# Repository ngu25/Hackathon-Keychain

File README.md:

# Hackathon-Keychain

This is a keychain made for the participants and giveaway!

This event & the keychain wouldn't have been possible without the amazing [team](https://www.linkedin.com/posts/srinivasan-m-421179179_hackathon-pcbcupid-glyph-activity-7355658636741758976-tHrb?utm_source=share&utm_medium=member_desktop&rcm=ACoAADTSA38BsfCnTXBQPUgEnAOWLHQZu77Voxg) that we had!

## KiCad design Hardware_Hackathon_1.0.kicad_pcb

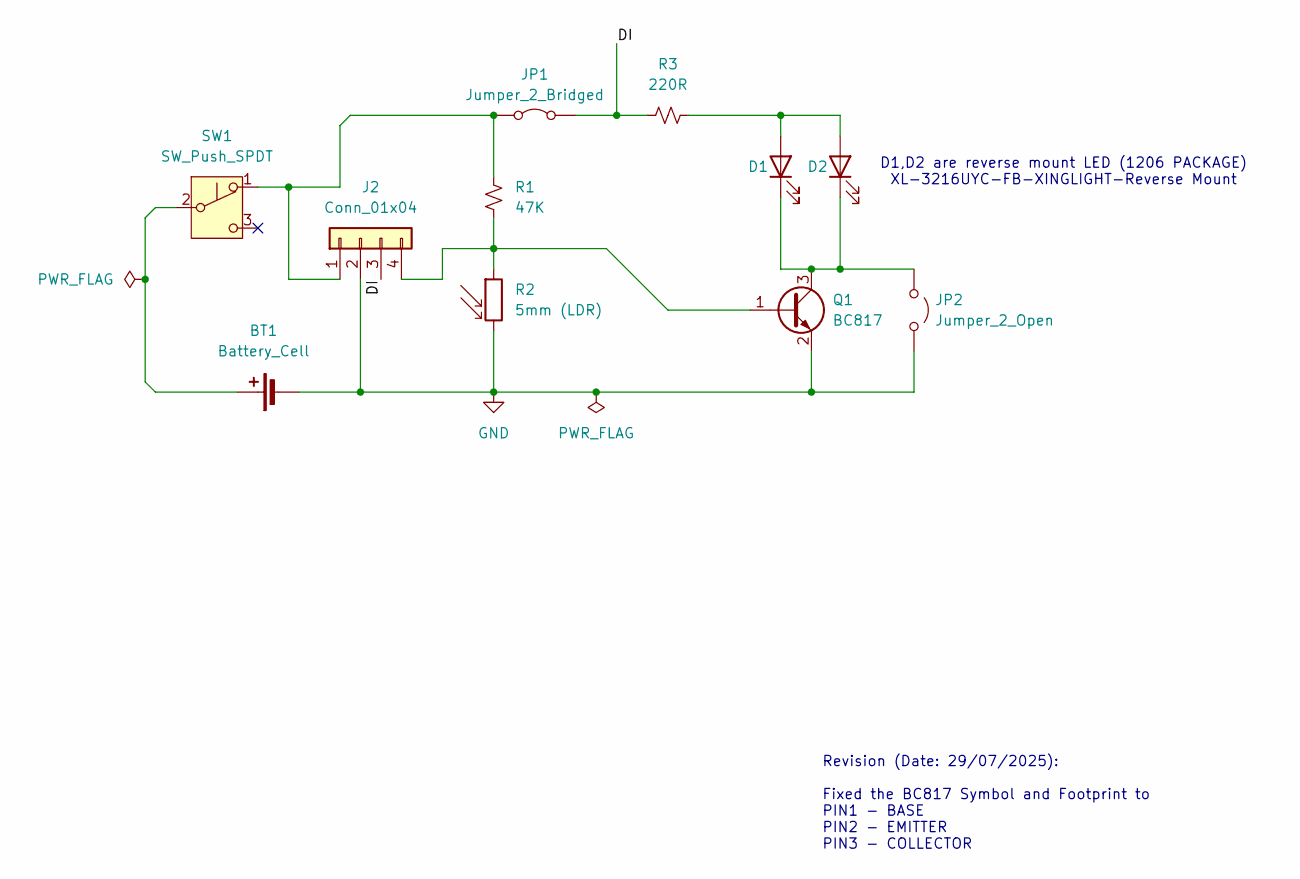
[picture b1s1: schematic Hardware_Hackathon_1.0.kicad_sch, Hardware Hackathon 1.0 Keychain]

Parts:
BT1: Battery_Cell; BAT_BAT-HLD-001
D1, D2: LED; LED_1206_3216Metric_ReverseMount_Hole1.8x2.4mm
J2: Conn_01x04; PinSocket_1x04_P2.54mm_Vertical
JP1: Jumper_2_Bridged; SolderJumper-2_P1.3mm_Bridged_RoundedPad1.0x1.5mm
JP2: Jumper_2_Open; SolderJumper-2_P1.3mm_Open_RoundedPad1.0x1.5mm
Q1: BC817; SOT-23
R1: 47K; R_0603_1608Metric_Pad0.98x0.95mm_HandSolder
R2: 5mm (LDR); R_LDR_5.1x4.3mm_P3.4mm_Vertical
R3: 220R; R_0603_1608Metric_Pad0.98x0.95mm_HandSolder
SW1: SW_Push_SPDT; SW_SPDT_PCM12

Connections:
/DI: J2.3, JP1.2 (B), R3.2
GND: BT1.2 (-), J2.2, JP2.2 (B), Q1.2 (E), R2.2
unnamed: BT1.1 (+), SW1.2 (B)
unnamed: D1.2 (A), D2.2 (A), R3.1
unnamed: D1.1 (K), D2.1 (K), JP2.1 (A), Q1.3 (C)
unnamed: J2.1, JP1.1 (A), R1.2, SW1.1 (A)
unnamed: J2.4, Q1.1 (B), R1.1, R2.1

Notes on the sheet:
D1,D2 are reverse mount LED (1206 PACKAGE) XL-3216UYC-FB-XINGLIGHT-Reverse Mount
Revision (Date: 29/07/2025): Fixed the BC817 Symbol and Footprint to PIN1 - BASE PIN2 - EMITTER PIN3 - COLLECTOR

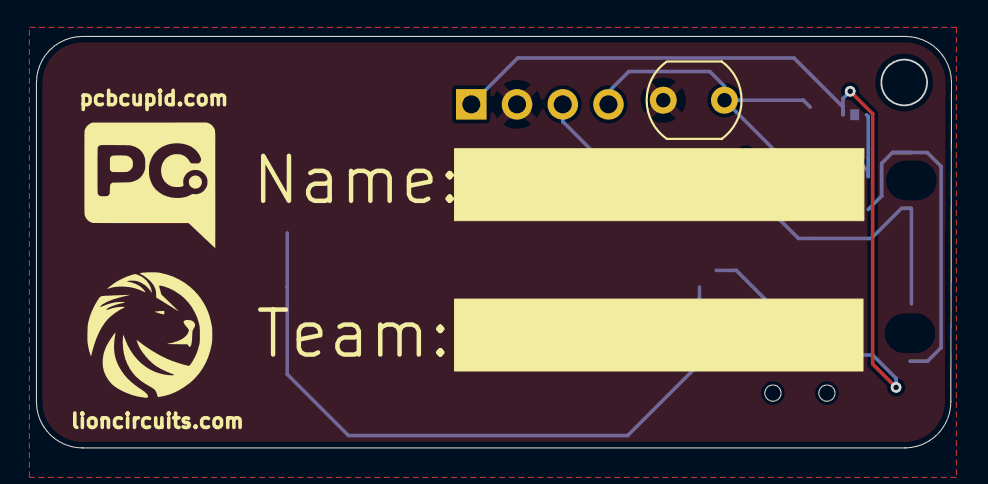
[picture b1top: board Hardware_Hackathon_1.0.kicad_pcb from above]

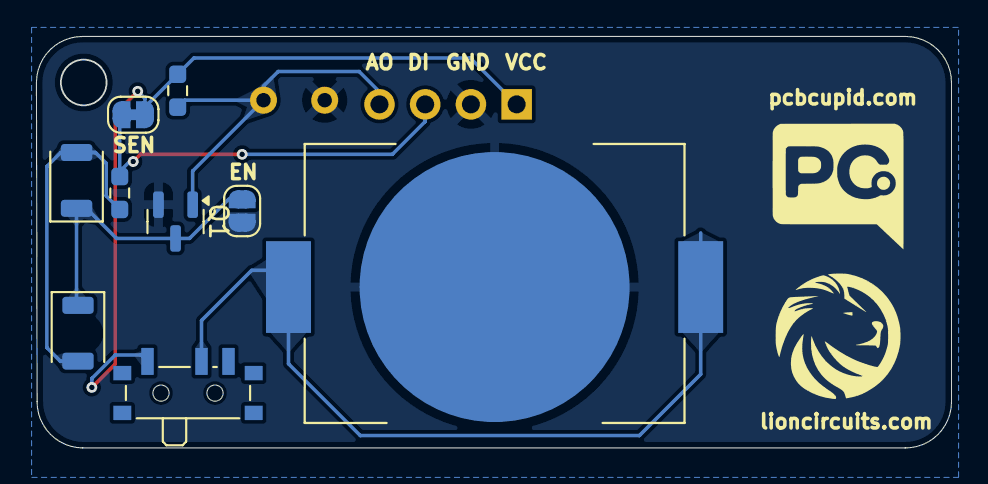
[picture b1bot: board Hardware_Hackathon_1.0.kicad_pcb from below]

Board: 2 copper layers, 50.8 x 22.8 mm, 15 parts (12 on the bottom side), 7 nets.

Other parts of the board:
Lion_circuits-1, Lion_circuits-1#2: LOGO; Lion_circuits_Logo
PCB_CUBID-1, PCB_CUBID-1#2: LOGO; PCB_CUBID

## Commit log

2025-07-29 added Kicad Files + Images
2025-07-29 fixed BC817 symbol and footprint pin reversal
